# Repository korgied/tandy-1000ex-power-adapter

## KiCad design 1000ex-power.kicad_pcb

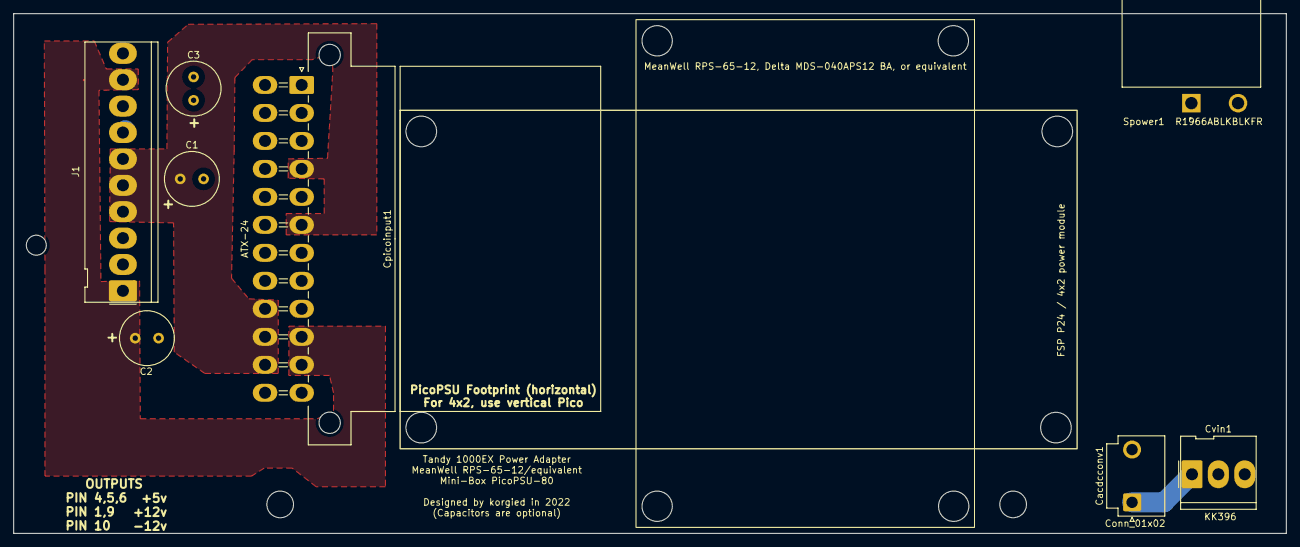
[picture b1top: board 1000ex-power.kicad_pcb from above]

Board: 2 copper layers, 191.0 x 78.0 mm, 9 parts (0 on the bottom side), 7 nets.

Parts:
C1, C2, C3: 330u 25v; C_Radial_D8.0mm_H7.0mm_P3.50mm
Cacdcconv1: Conn_01x02; JST_VH_B2P3-VH_1x02_P7.92mm_Vertical
Cpicoinput1: ATX-24; Molex_Mini-Fit_Jr_5569-24A1_2x12_P4.20mm_Horizontal
Cvin1: Conn_01x03; Molex_KK-396_5273-03A_1x03_P3.96mm_Vertical
FSP P24 / 4x2 power module: FSP_P24A_101.6x50.8
J1: Coutput; Molex_KK-396_5273-10A_1x10_P3.96mm_Vertical
Spower1: R1966ABLKBLKFR; SW_R1966ABLKBLKFR

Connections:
/+5V: C1.2, Cpicoinput1.4 (+5V), Cpicoinput1.6 (+5V), Cpicoinput1.21 (+5V), Cpicoinput1.22 (+5V), Cpicoinput1.23 (+5V), J1.4, J1.5, J1.6
/+12v: C2.1, Cpicoinput1.10 (+12V), Cpicoinput1.11 (+12V), J1.1, J1.9
/-12v: C3.2, Cpicoinput1.14 (-12V), J1.10
/GND: C1.1, C2.2, C3.1, Cpicoinput1.3 (GND), Cpicoinput1.5 (GND), Cpicoinput1.7 (GND), Cpicoinput1.15 (GND), Cpicoinput1.16 (PS_ON#), Cpicoinput1.17 (GND), Cpicoinput1.18 (GND), Cpicoinput1.19 (GND), Cpicoinput1.24 (GND), J1.2, J1.3, J1.7, J1.8
/hot: Cvin1.3, Spower1.1A
/neutral: Cacdcconv1.1, Cvin1.1
/switched_hot: Cacdcconv1.2, Spower1.1

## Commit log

2022-10-07 Added project
